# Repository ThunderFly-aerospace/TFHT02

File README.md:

# TFHT02 - Miniature UAV Humidity and Temperature Sensor

The TFHT02 hygrometer sensor offers flexible integration options. It can be directly connected to a Pixhawk autopilot with PX4 firmware, or it can be used as a sensor for the [TF-ATMON monitoring system](https://www.thunderfly.cz/tf-atmon.html). The TFHT02 is optimized for fast response and reduced sensitivity to solar radiation, making it suitable for meteorological measurements of atmospheric profiles, where rapid environmental changes require fast response to maintain high measurement accuracy.

### Atmospheric sounding

The TFHT02 sensor is designed for [direct atmospheric sounding](https://en.wikipedia.org/wiki/Atmospheric_sounding). Here is an example of measured data taken by [TF-G2 autogyro](https://www.thunderfly.cz/tf-g2.html).

## Where to get it?

The TFHT02 is commercially available from [ThunderFly s.r.o.](https://www.thunderfly.cz/). For a commercial quotation or support, contact us by email at sale@thunderfly.cz or shop at [Tindie store](https://www.tindie.com/products/thunderfly/tfht01-aerial-hygrometer-and-thermometer/).

## Parameters

| Parameter | Value | Description |
|-----------|-------|-------------|
| Sensing element | [SHT45](https://sensirion.com/media/documents/33FD6951/662A593A/HT_DS_Datasheet_SHT4x.pdf) | Other possible sensors are SHT40 or SHT41 |
| Typical accuracy | 1 %RH and 0.1 °C | |
| Repeatability | 0.15 %RH , 0.08 °C | The stated repeatability is 3 times the standard deviation (3σ) of multiple consecutive measurements at constant ambient conditions. |
| Operating temperature range| 0 °C - +65 °C | Sensor physically measures in range -40°C to +120°C with reduced accuracy |
| Operating humidity range| 0-100 % | At humidity above 80% the performance of the sensor could be degraded in case of prolonged periods |
| I2C connector | 4-pin JST-GH | The second connector could be installed on the opposite side |
| I2C address | 0x44 | |
| Storage temperature range| -20 °C - +40 °C |  |
| Operational input voltage | 3.6 - 5.4V | Overvoltage is internally protected by zener diode |
| Mass | 2 g | PCB without cabling |
| Dimensions | 30 x 15 x 6.5 mm |  PCB |
| Weather resistance | IP40 | External connectors fully occupied. |

## Sensor Design

The TFHT02 sensor is designed with an emphasis on fast response time and minimal sensitivity to solar radiation. This is achieved by reducing the thermal mass around the sensing element, allowing it to rapidly react to changes in ambient conditions. Additionally, the sensor is positioned in a way that maximizes its contact surface with the surrounding airflow, ensuring efficient heat exchange and accurate real-time measurements, which are critical for meteorological applications, especially for atmospheric profiling.

### Schematics

## Usage in PX4 autopilot firmware

The PX4 autopilot firmware supports the sensor. Multiple sensors can be connected to one autopilot. The measured data could be sent to the ground station and at the same time logged in the onboard ulog file. Sensor support can be enabled by setting the [SENS_EN_SHT4X](http://docs.px4.io/master/en/advanced_config/parameter_reference.html#SENS_EN_SHT3X) parameter to 1.

### Driver Commands Examples

CLI usage example:

    sht4x start -X

Start the sensor driver on the external bus

    sht4x status

Print driver status

    sht4x values

Print the last measured values

    sht4x reset

Reinitialize senzor, reset flags

### PX4 Driver Usage

```
sht4x <command> [arguments...]
 Commands:
   start
     [-I]        Internal I2C bus(es)
     [-X]        External I2C bus(es)
     [-b <val>]  board-specific bus (default=all) (external SPI: n-th bus
                 (default=1))
     [-f <val>]  bus frequency in kHz
     [-q]        quiet startup (no message if no device found)
     [-a <val>]  I2C address
                 default: 68
     [-k]        If initialization (probing) fails, keep retrying periodically

   stop

   status        print status info

   values        Print actual data

   reset         Reinitialize sensor
```

## Usage in Ardupilot firmware

In the Ardupilot firmware, the corresponding sht4x driver for TFHT02 is currently missing. The contributions are welcomed.

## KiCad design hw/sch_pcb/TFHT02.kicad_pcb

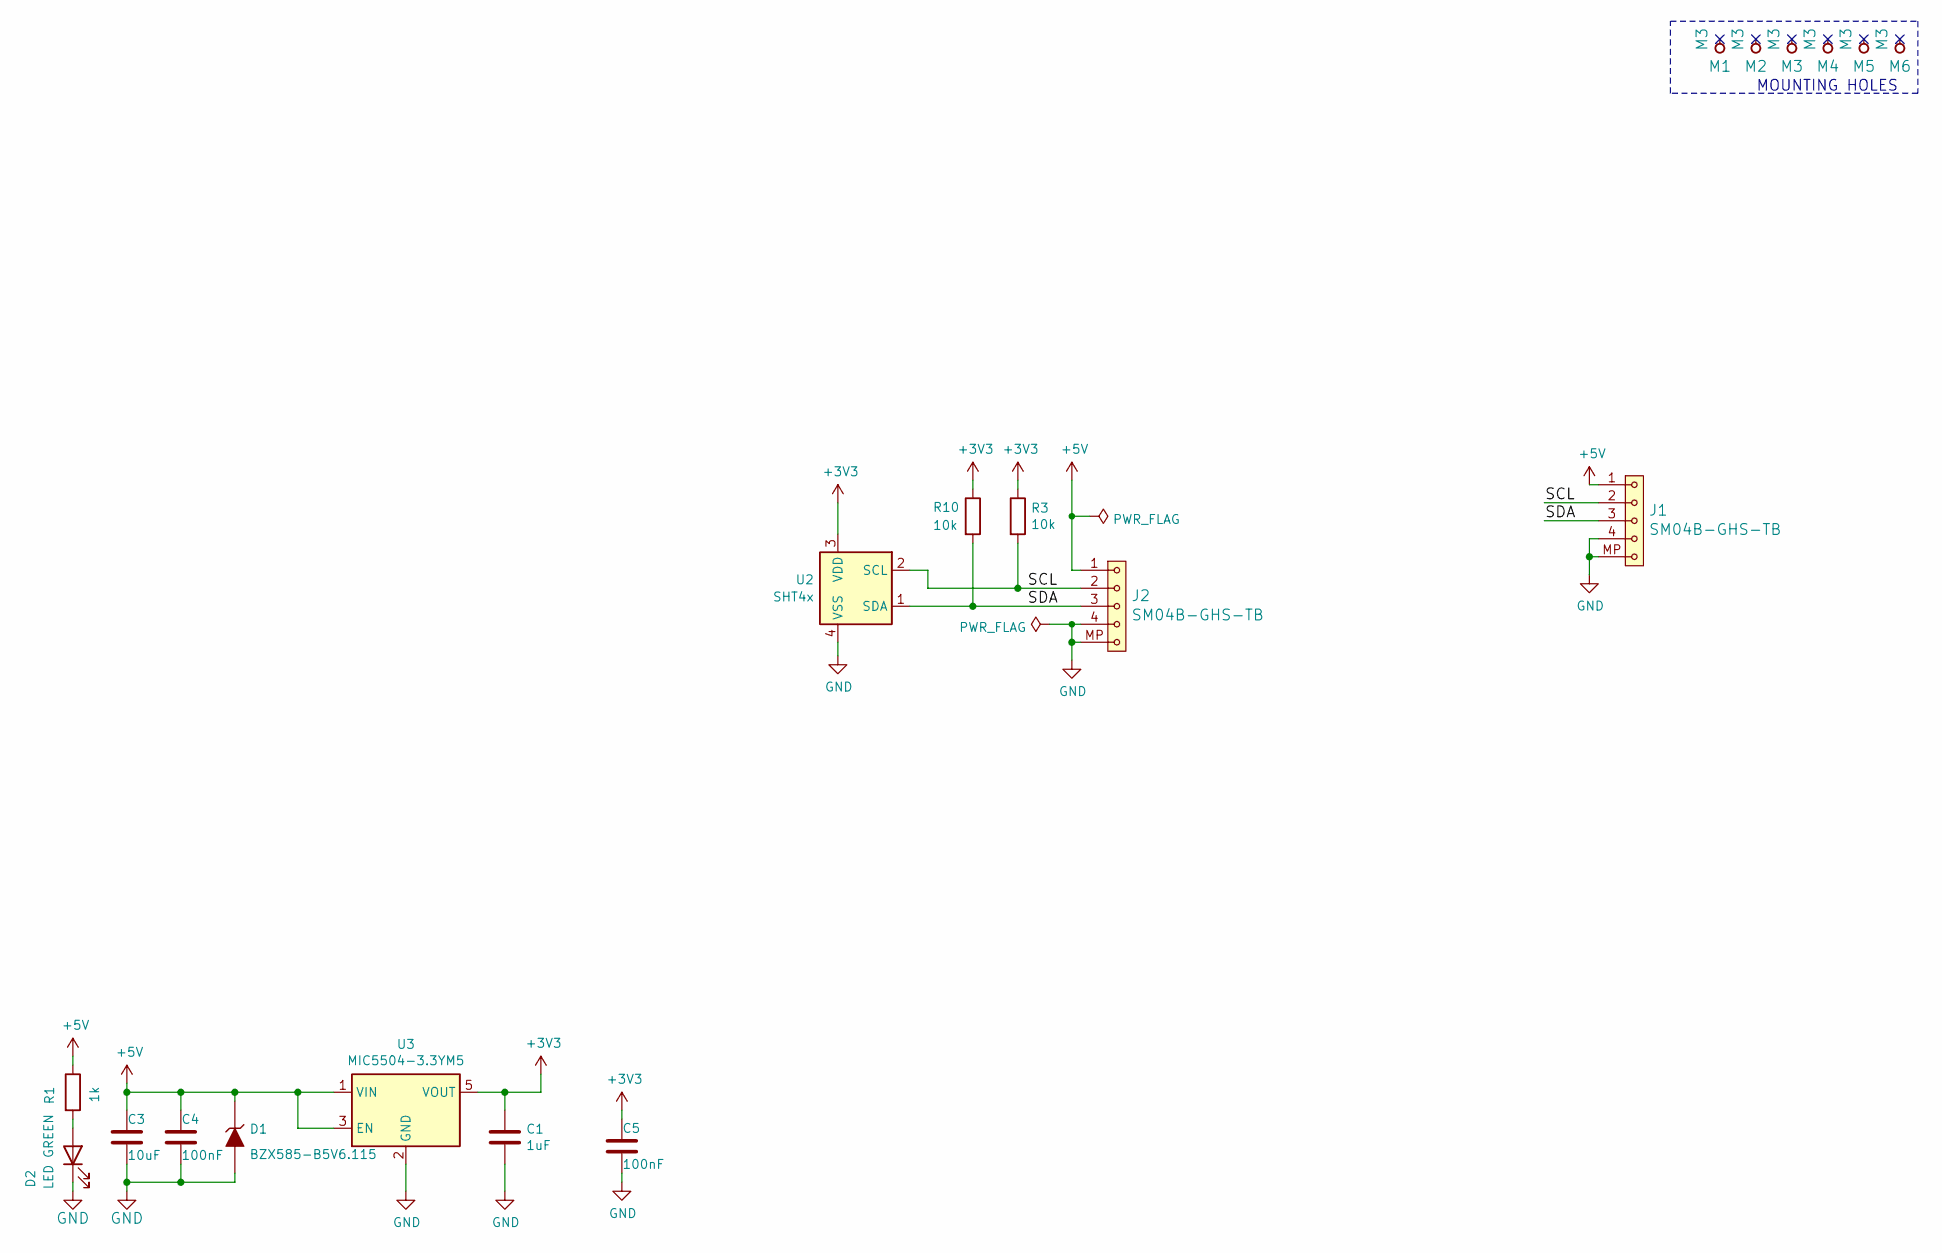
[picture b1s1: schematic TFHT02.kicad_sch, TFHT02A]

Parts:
C1: 1uF; C_0603_1608Metric
C3: 10uF; C_0805_2012Metric
C4, C5: 100nF; C_0603_1608Metric
D1: BZX585-B5V6.115; D_SOD-523
D2: LED GREEN; LED_1206_mill
J1, J2: SM04B-GHS-TB; JST_GH_SM04B-GHS-TB_1x04-1MP_P1.25mm_Horizontal
M1, M2, M3, M4, M5, M6: M3; dira_3mm
R1: 1k; R_0603_1608Metric
R3, R10: 10k; R_0603_1608Metric
U2: SHT4x; Sensirion_DFN-4_1.5x1.5mm_P0.8mm_SHT4x_NoCentralPad
U3: MIC5504-3.3YM5; SOT-23-5

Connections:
+3V3: C1.1, C5.1, R3.1, R10.1, U2.3 (VDD), U3.5 (VOUT)
+5V: C3.1, C4.1, D1.1 (K), J1.1, J2.1, R1.1, U3.1 (VIN), U3.3 (EN)
/SCL: J1.2, J2.2, R3.2, U2.2 (SCL)
/SDA: J1.3, J2.3, R10.2, U2.1 (SDA)
GND: C1.2, C3.2, C4.2, C5.2, D1.2 (A), D2.1 (K), J1.4, J1.MP, J2.4, J2.MP, U2.4 (VSS), U3.2 (GND)
unnamed: D2.2 (A), R1.2

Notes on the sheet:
MOUNTING HOLES

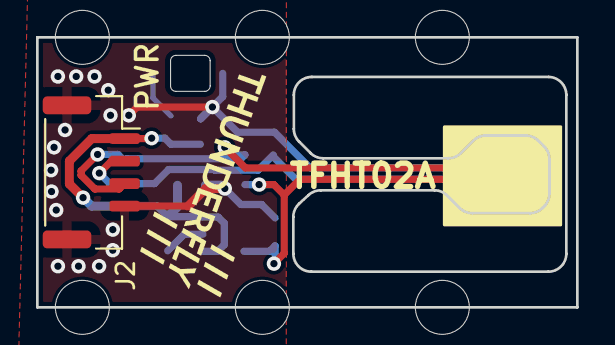
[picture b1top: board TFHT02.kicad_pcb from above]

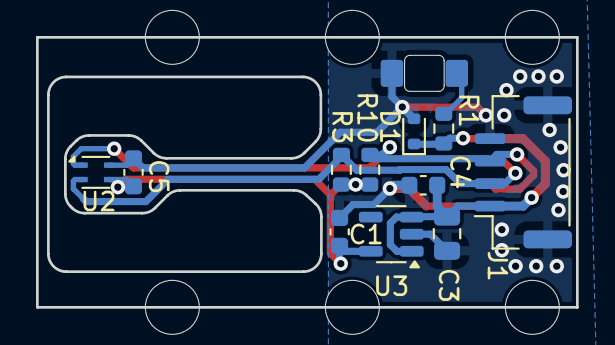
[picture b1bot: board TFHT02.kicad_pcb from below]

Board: 2 copper layers, 30.0 x 15.0 mm, 19 parts (12 on the bottom side), 6 nets.

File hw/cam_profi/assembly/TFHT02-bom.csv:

Component,Description,Part,References,Value,Footprint,Quantity Per PCB,Datasheet,ust_id
1,Unpolarized capacitor,C,C4C5,100nF,C_0603_1608Metric,2,~,5c70984812875079b91f8bf2
2,Unpolarized capacitor,C,C1,1uF,C_0603_1608Metric,1,~,5c70984812875079b91f8bc2
3,Unpolarized capacitor,C,C3,10uF,C_0805_2012Metric,1,~,5c70984812875079b91f8bbd
4,,D_ZENER,D1,BZX585-B5V6.115,D_SOD-523,1,,60879d38128750769ee58e48
5,Light emitting diode,LED,D2,LED GREEN,LED_1206_mill,1,~,5c70984412875079b91f8895
6,,SM04B-GHS-TB,J1J2,SM04B-GHS-TB,JST_GH_SM04B-GHS-TB_1x04-1MP_P1.25mm_Horizontal,2,,5c86273d1287500b4e0280be
7,Resistor,R,R1,1k,R_0603_1608Metric,1,~,5c70984512875079b91f8957
8,Resistor,R,R3R10,10k,R_0603_1608Metric,2,~,5c70984512875079b91f8962
9,"300mA Low-dropout Voltage Regulator, Vout 3.3V, Vin up to 5.5V, SOT-23",MIC5504-3.3YM5,U3,MIC5504-3.3YM5,SOT-23-5,1,http://ww1.microchip.com/downloads/en/DeviceDoc/MIC550X.pdf,5c7255e81287500b4e112ea2
10,"Digital Humidity and Temperature Sensor, +/-1%RH, +/-0.1degC, I2C, 1.08-3.6V, 16bit, DFN-4",SHT4x,U2,SHT4x,Sensirion_DFN-4_1.5x1.5mm_P0.8mm_SHT4x_NoCentralPad,1,https://www.tme.eu/Document/c90a92e7875700dbf5278abff1cc96dc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,65227831462c6d9e720559a1

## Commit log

2024-07-23 The firstly routed PCB with rought outline.
2024-07-23 Improved layout and geometry.
2024-07-23 Fillet radius of internal slot.
2024-07-23 Updating KiCAD actions.
2024-07-23 Update actions products
2024-07-23 Improve documentation.
2024-07-24 Update workflow files
2024-09-10 add step file
2025-01-12 Update driver name in readme.
2025-01-12 Improve readme and better describe the design.
2025-01-12 Update README.md
    Fix mistakes.
